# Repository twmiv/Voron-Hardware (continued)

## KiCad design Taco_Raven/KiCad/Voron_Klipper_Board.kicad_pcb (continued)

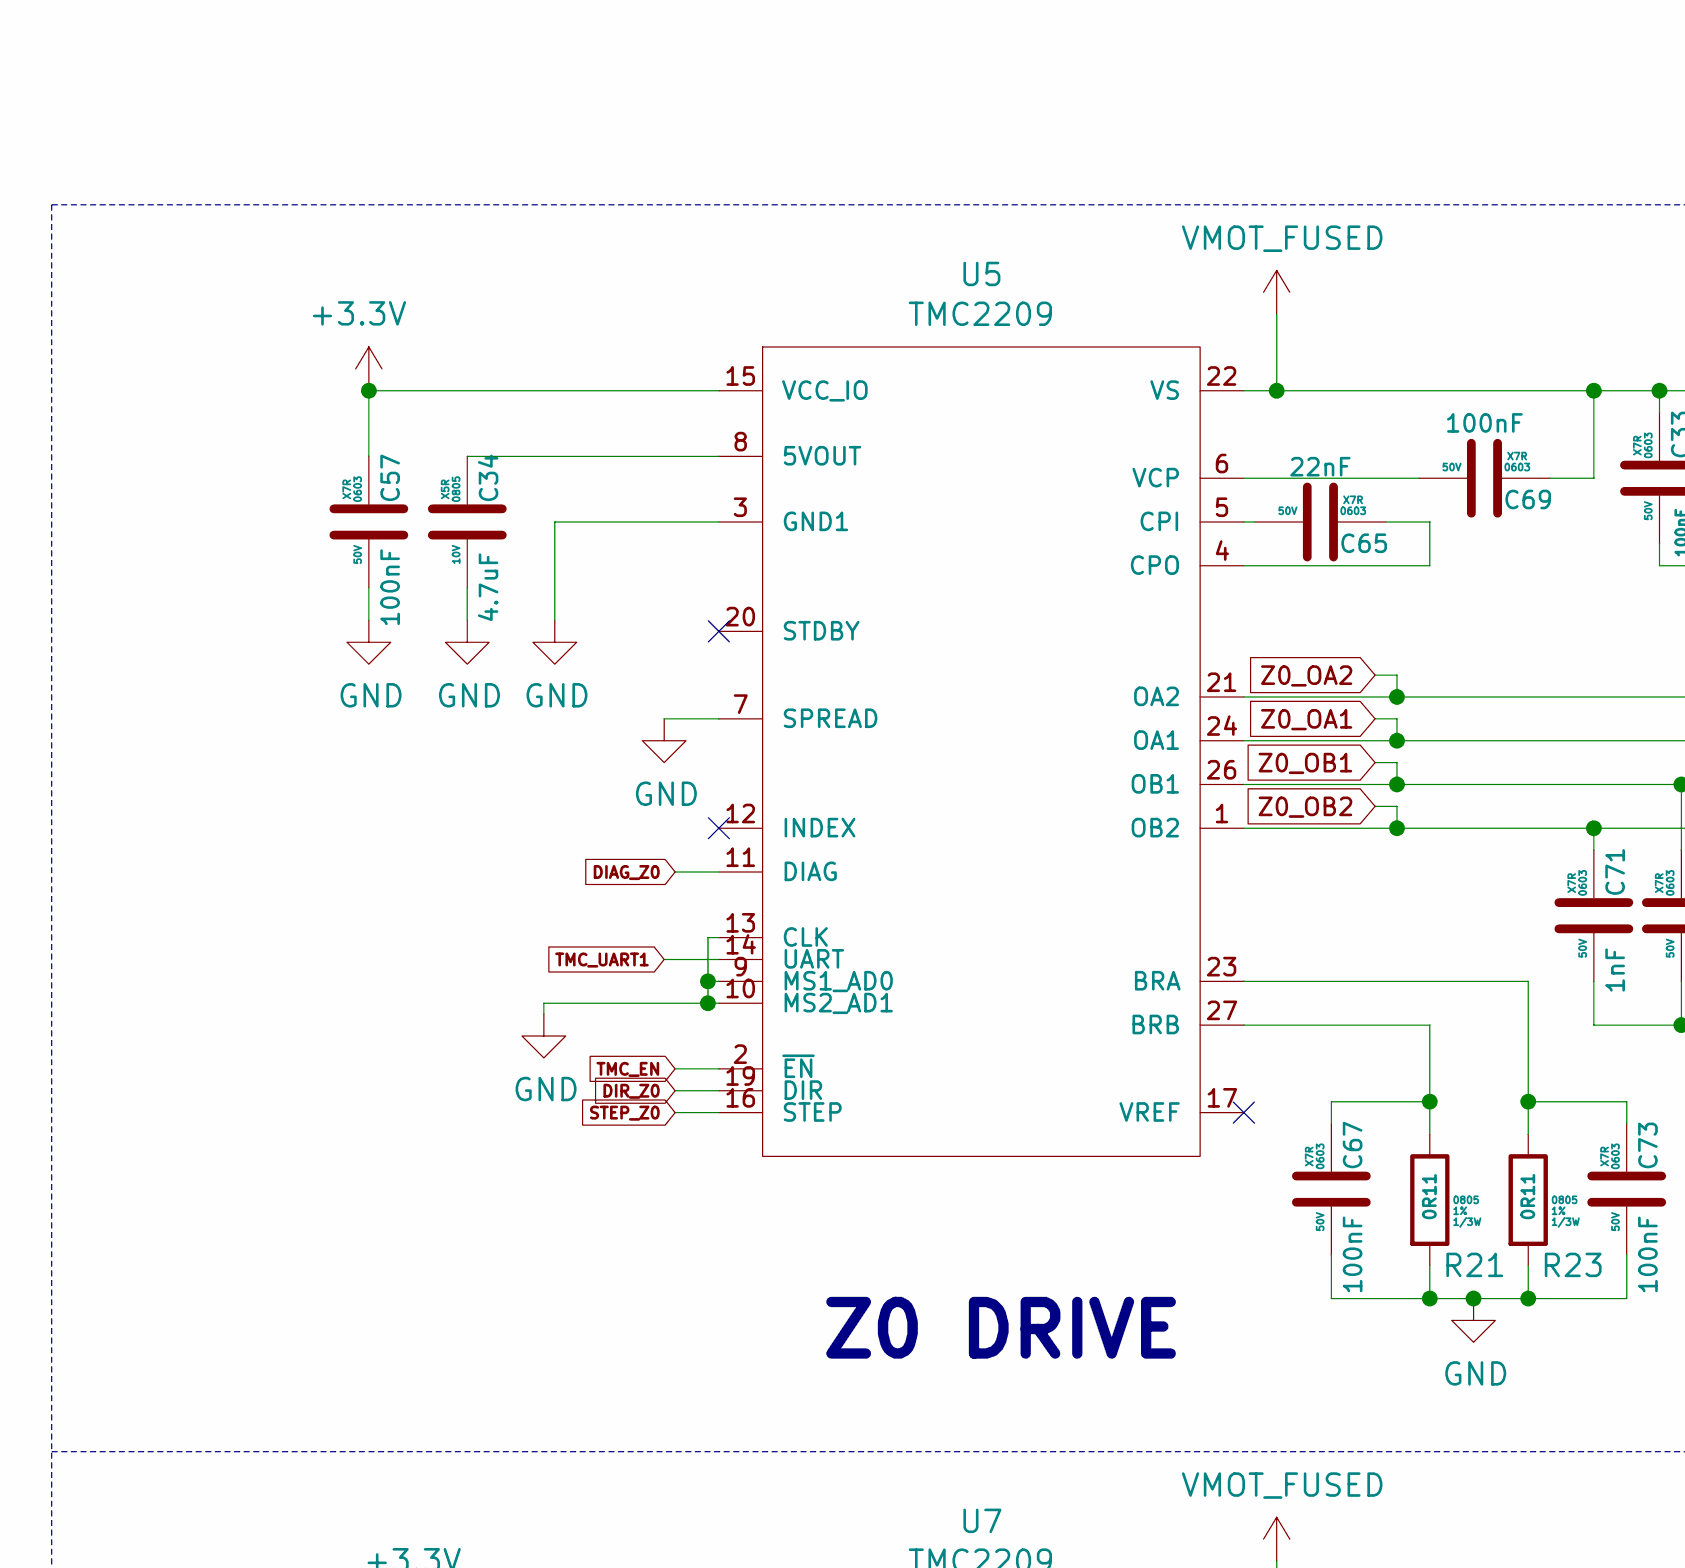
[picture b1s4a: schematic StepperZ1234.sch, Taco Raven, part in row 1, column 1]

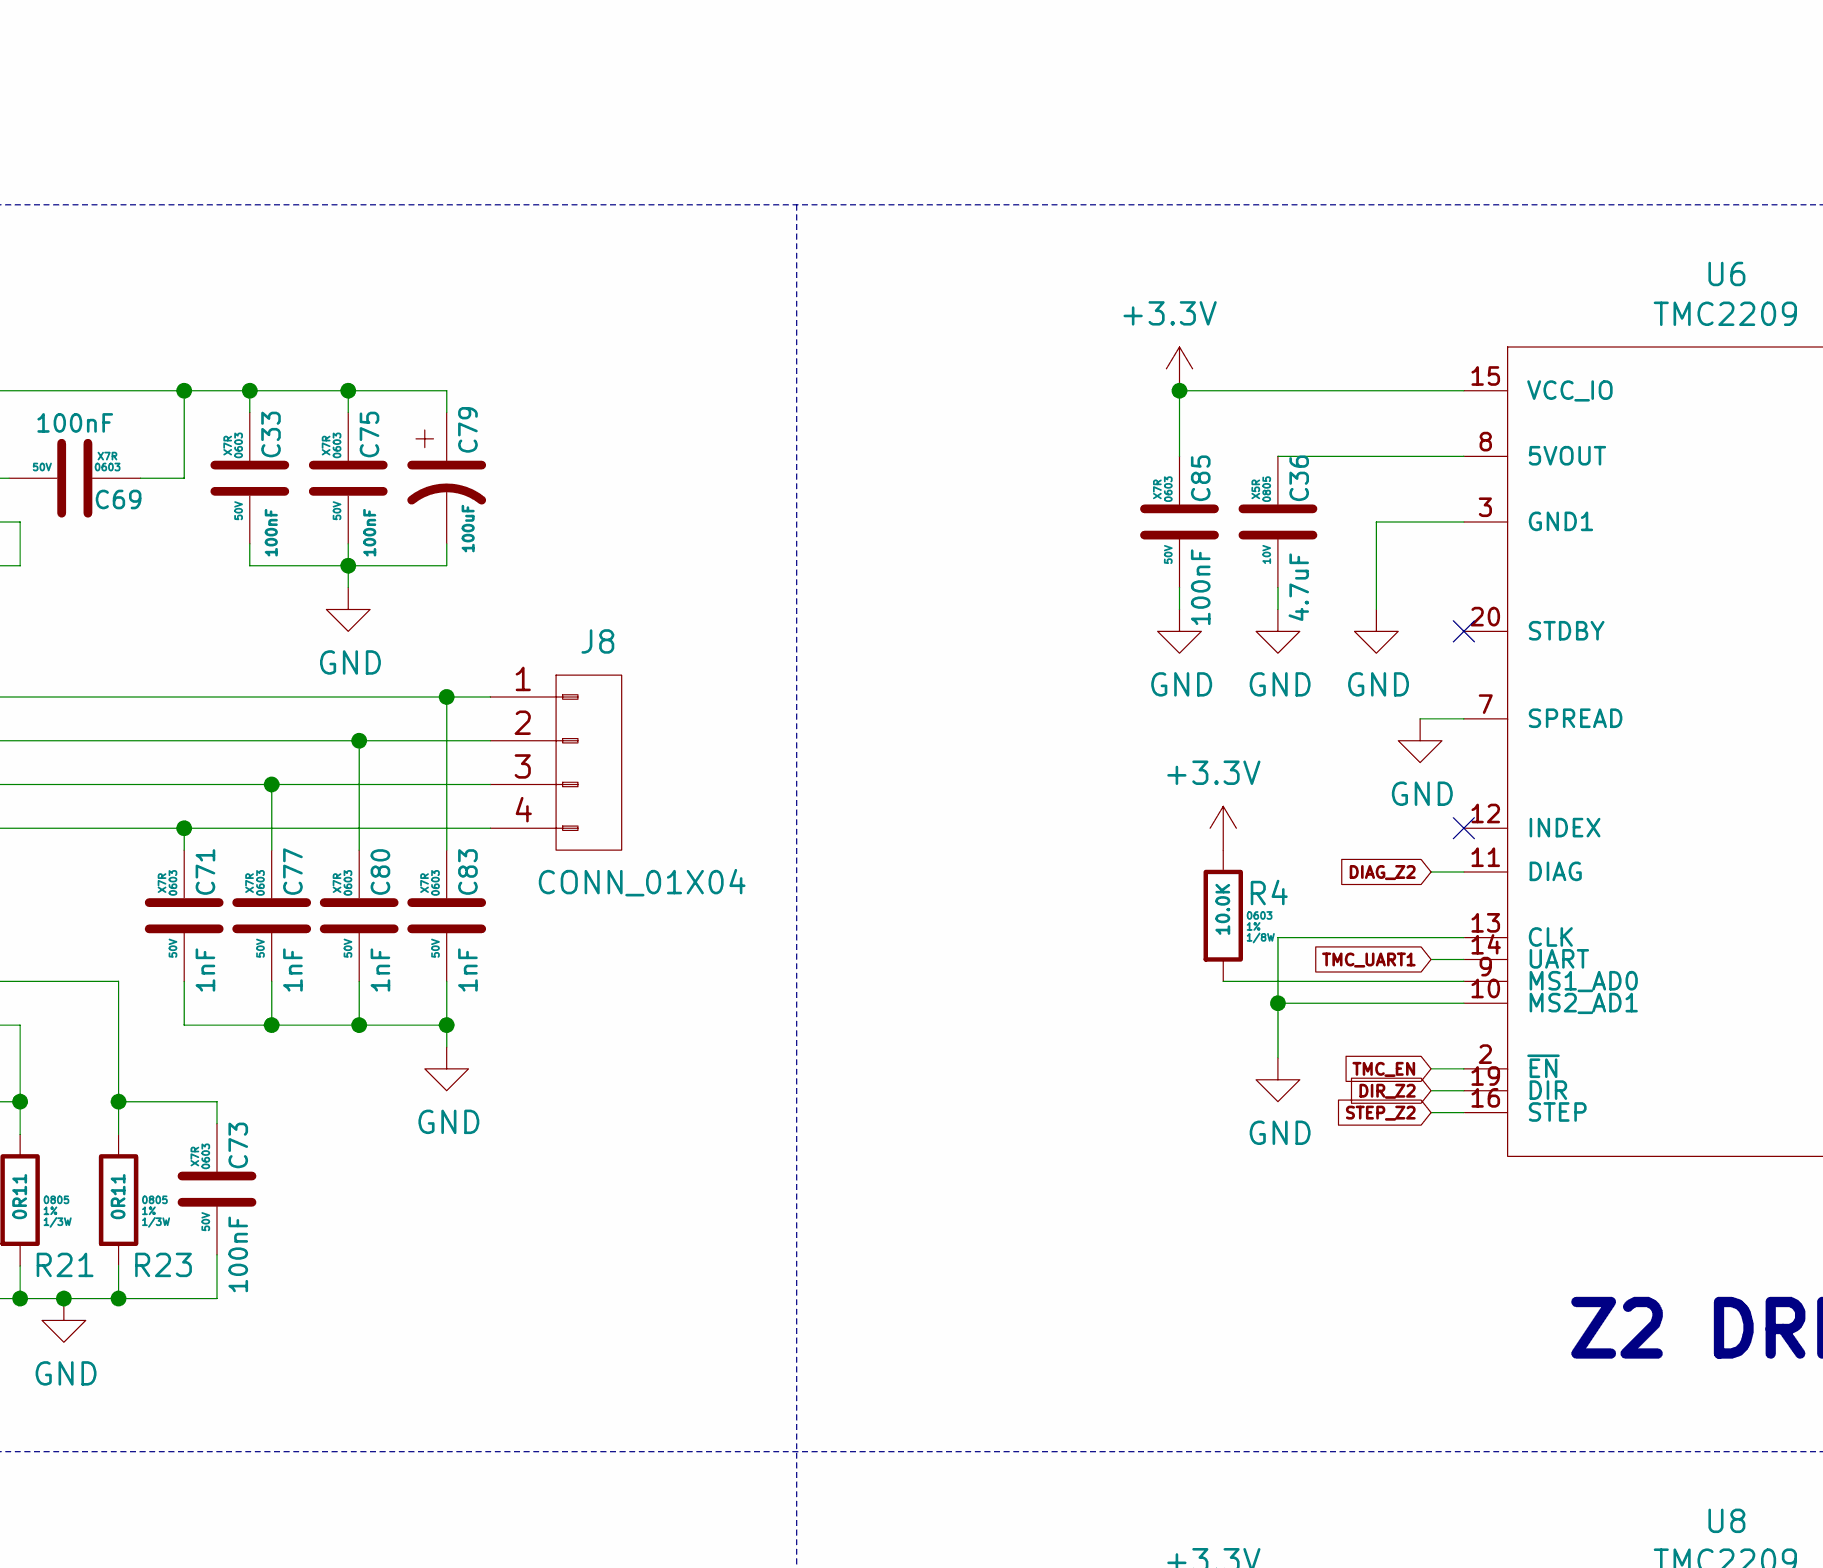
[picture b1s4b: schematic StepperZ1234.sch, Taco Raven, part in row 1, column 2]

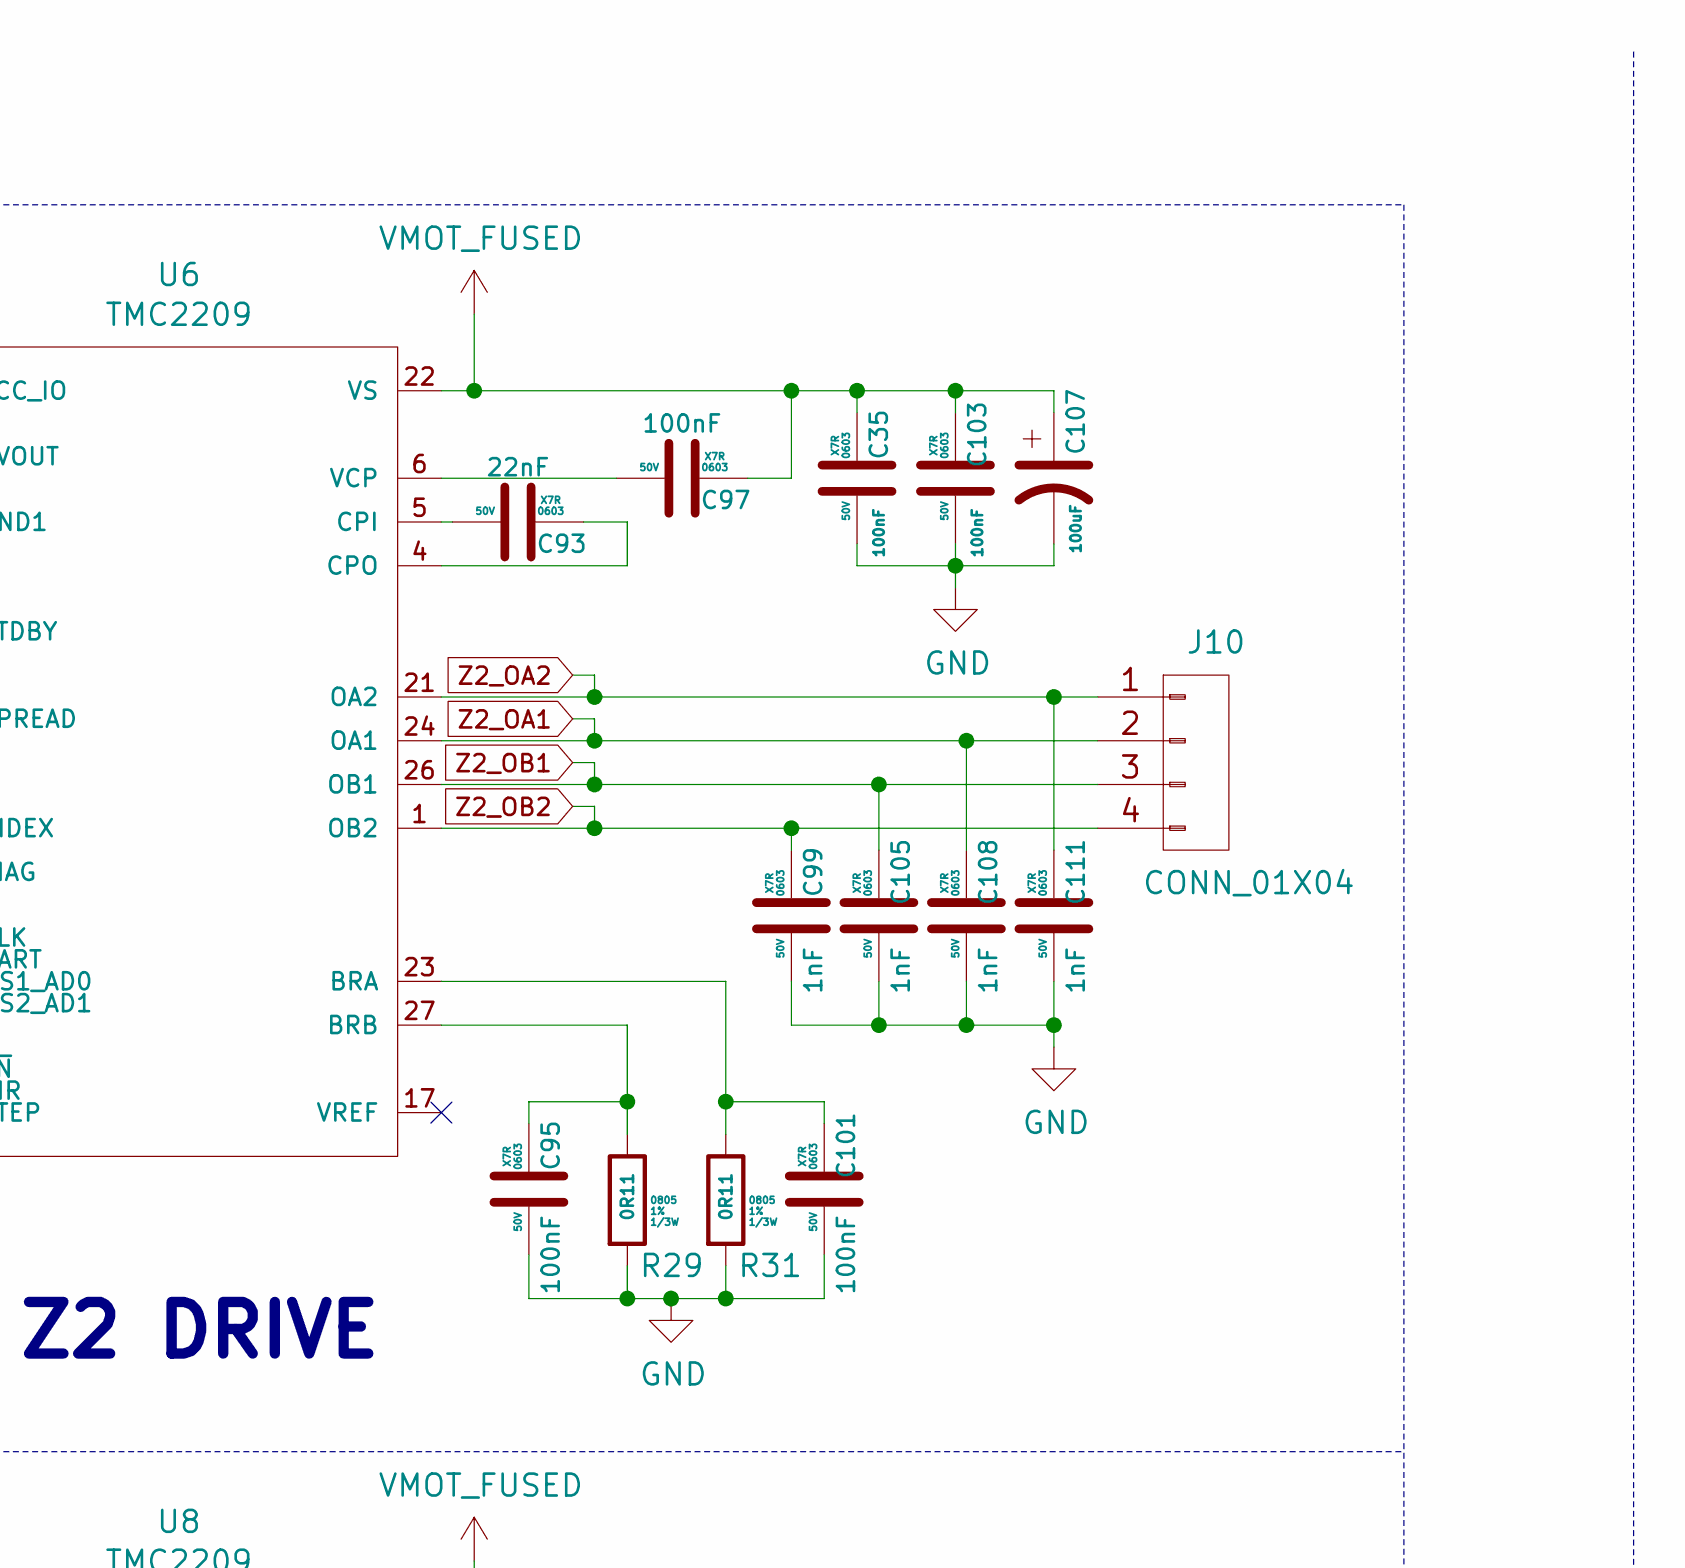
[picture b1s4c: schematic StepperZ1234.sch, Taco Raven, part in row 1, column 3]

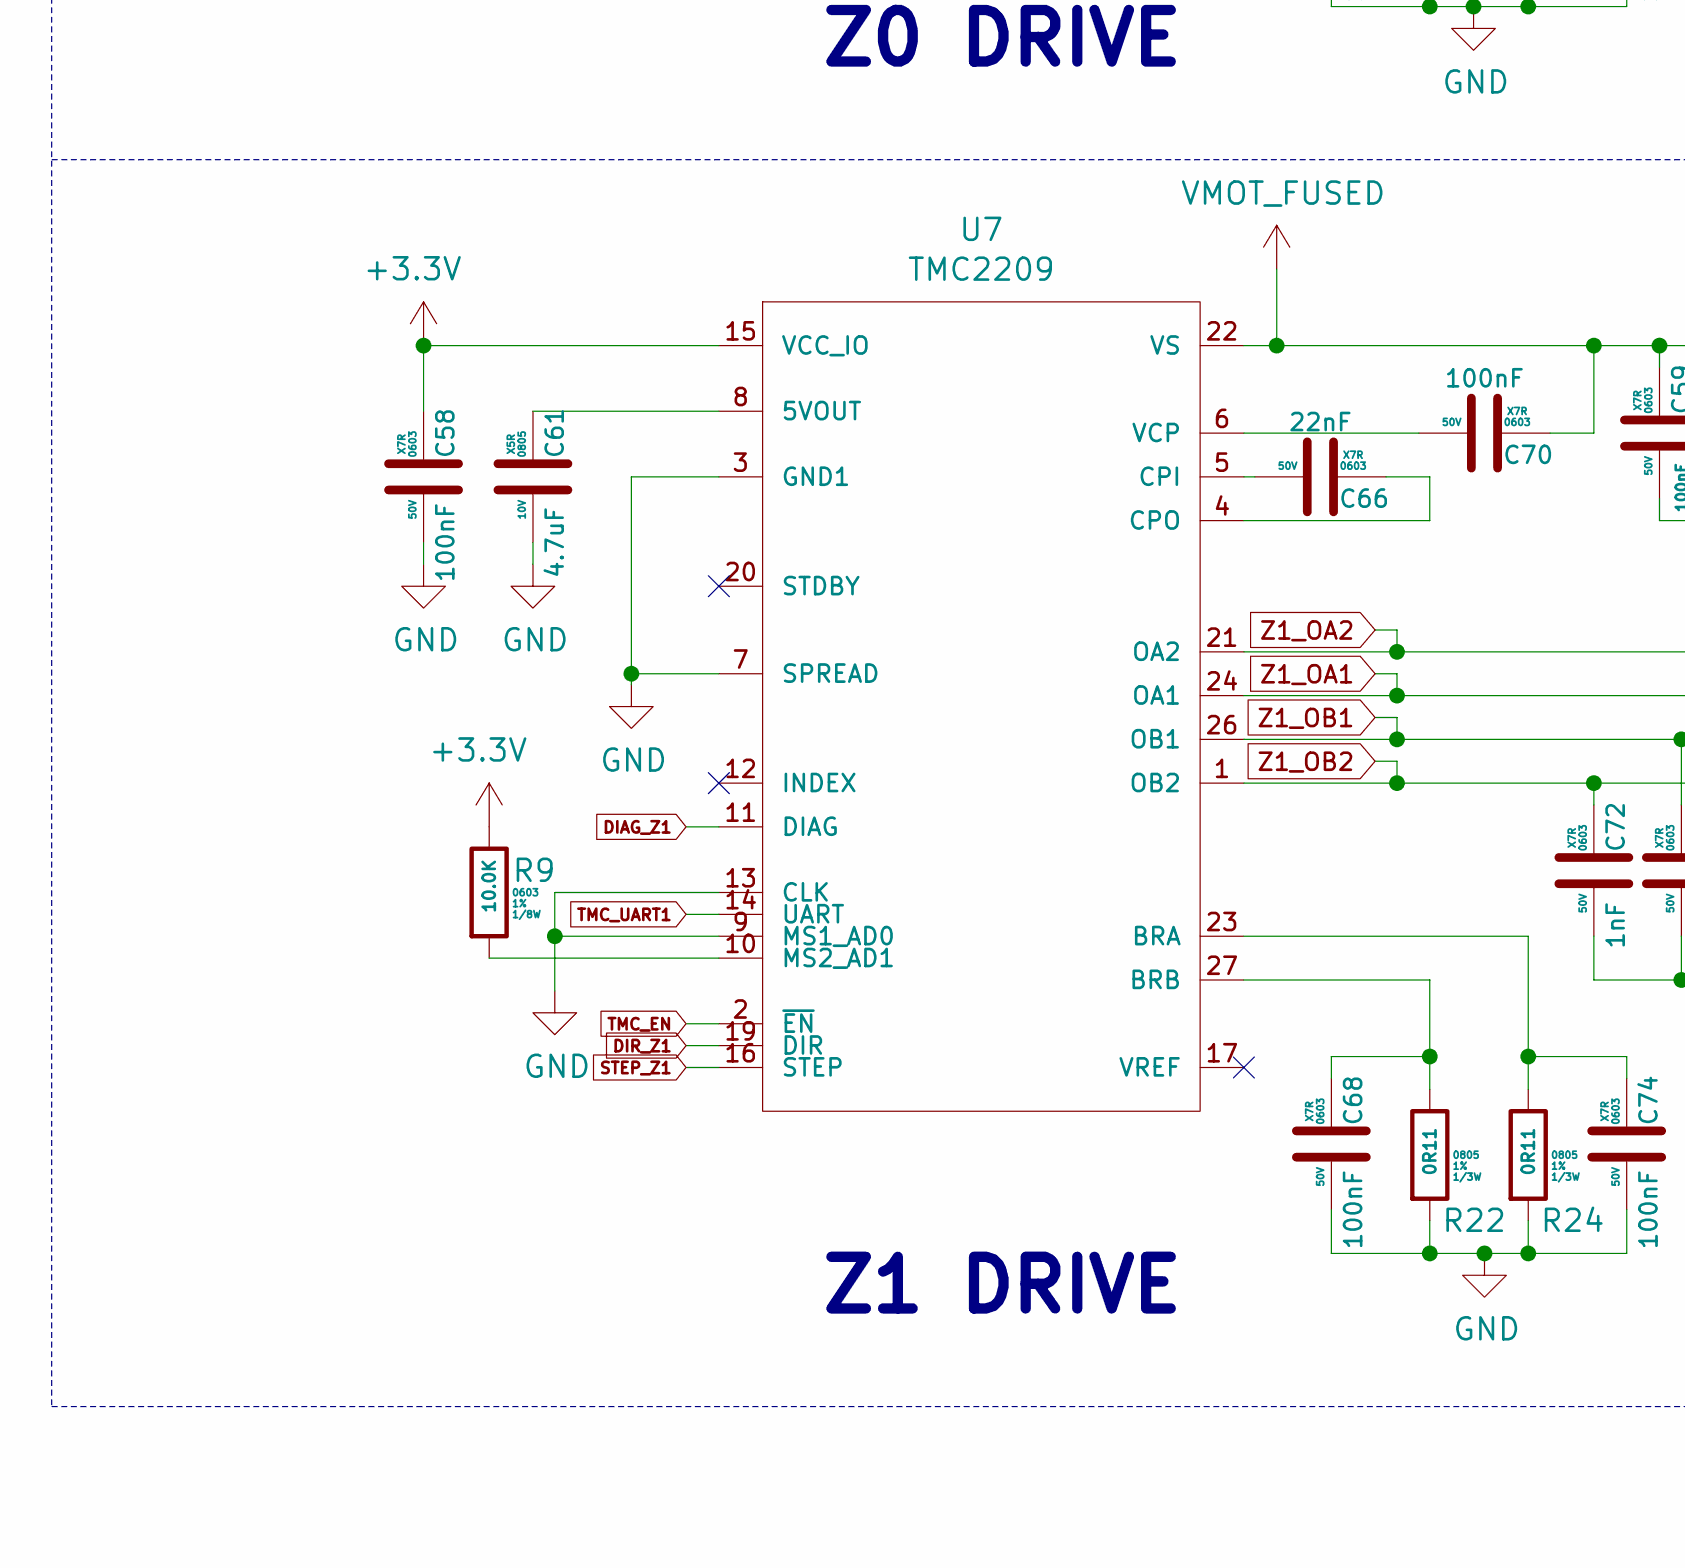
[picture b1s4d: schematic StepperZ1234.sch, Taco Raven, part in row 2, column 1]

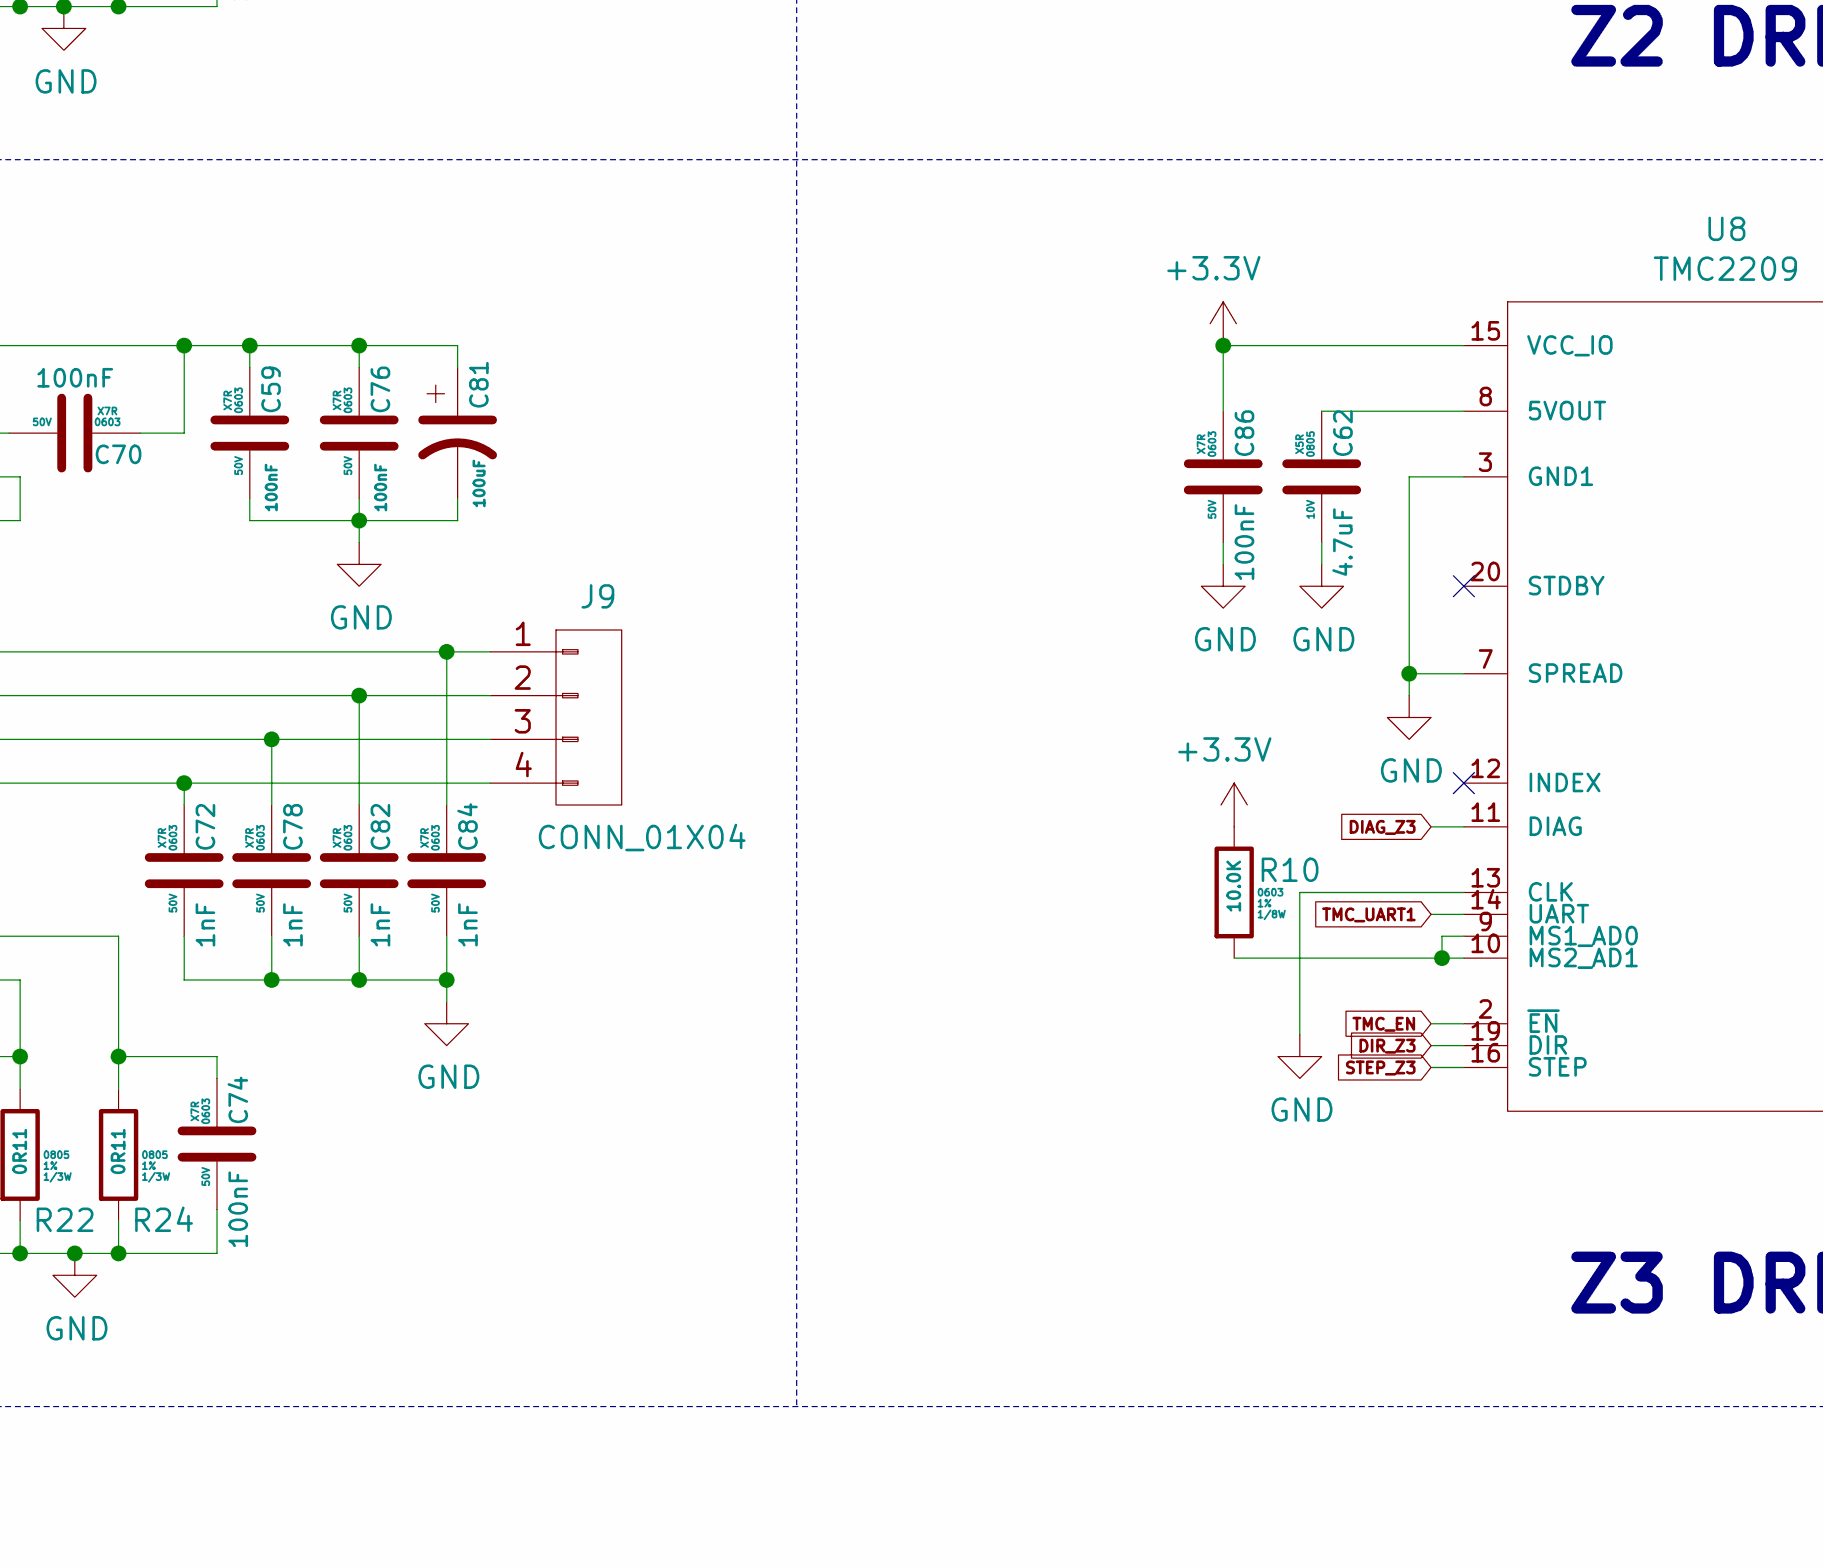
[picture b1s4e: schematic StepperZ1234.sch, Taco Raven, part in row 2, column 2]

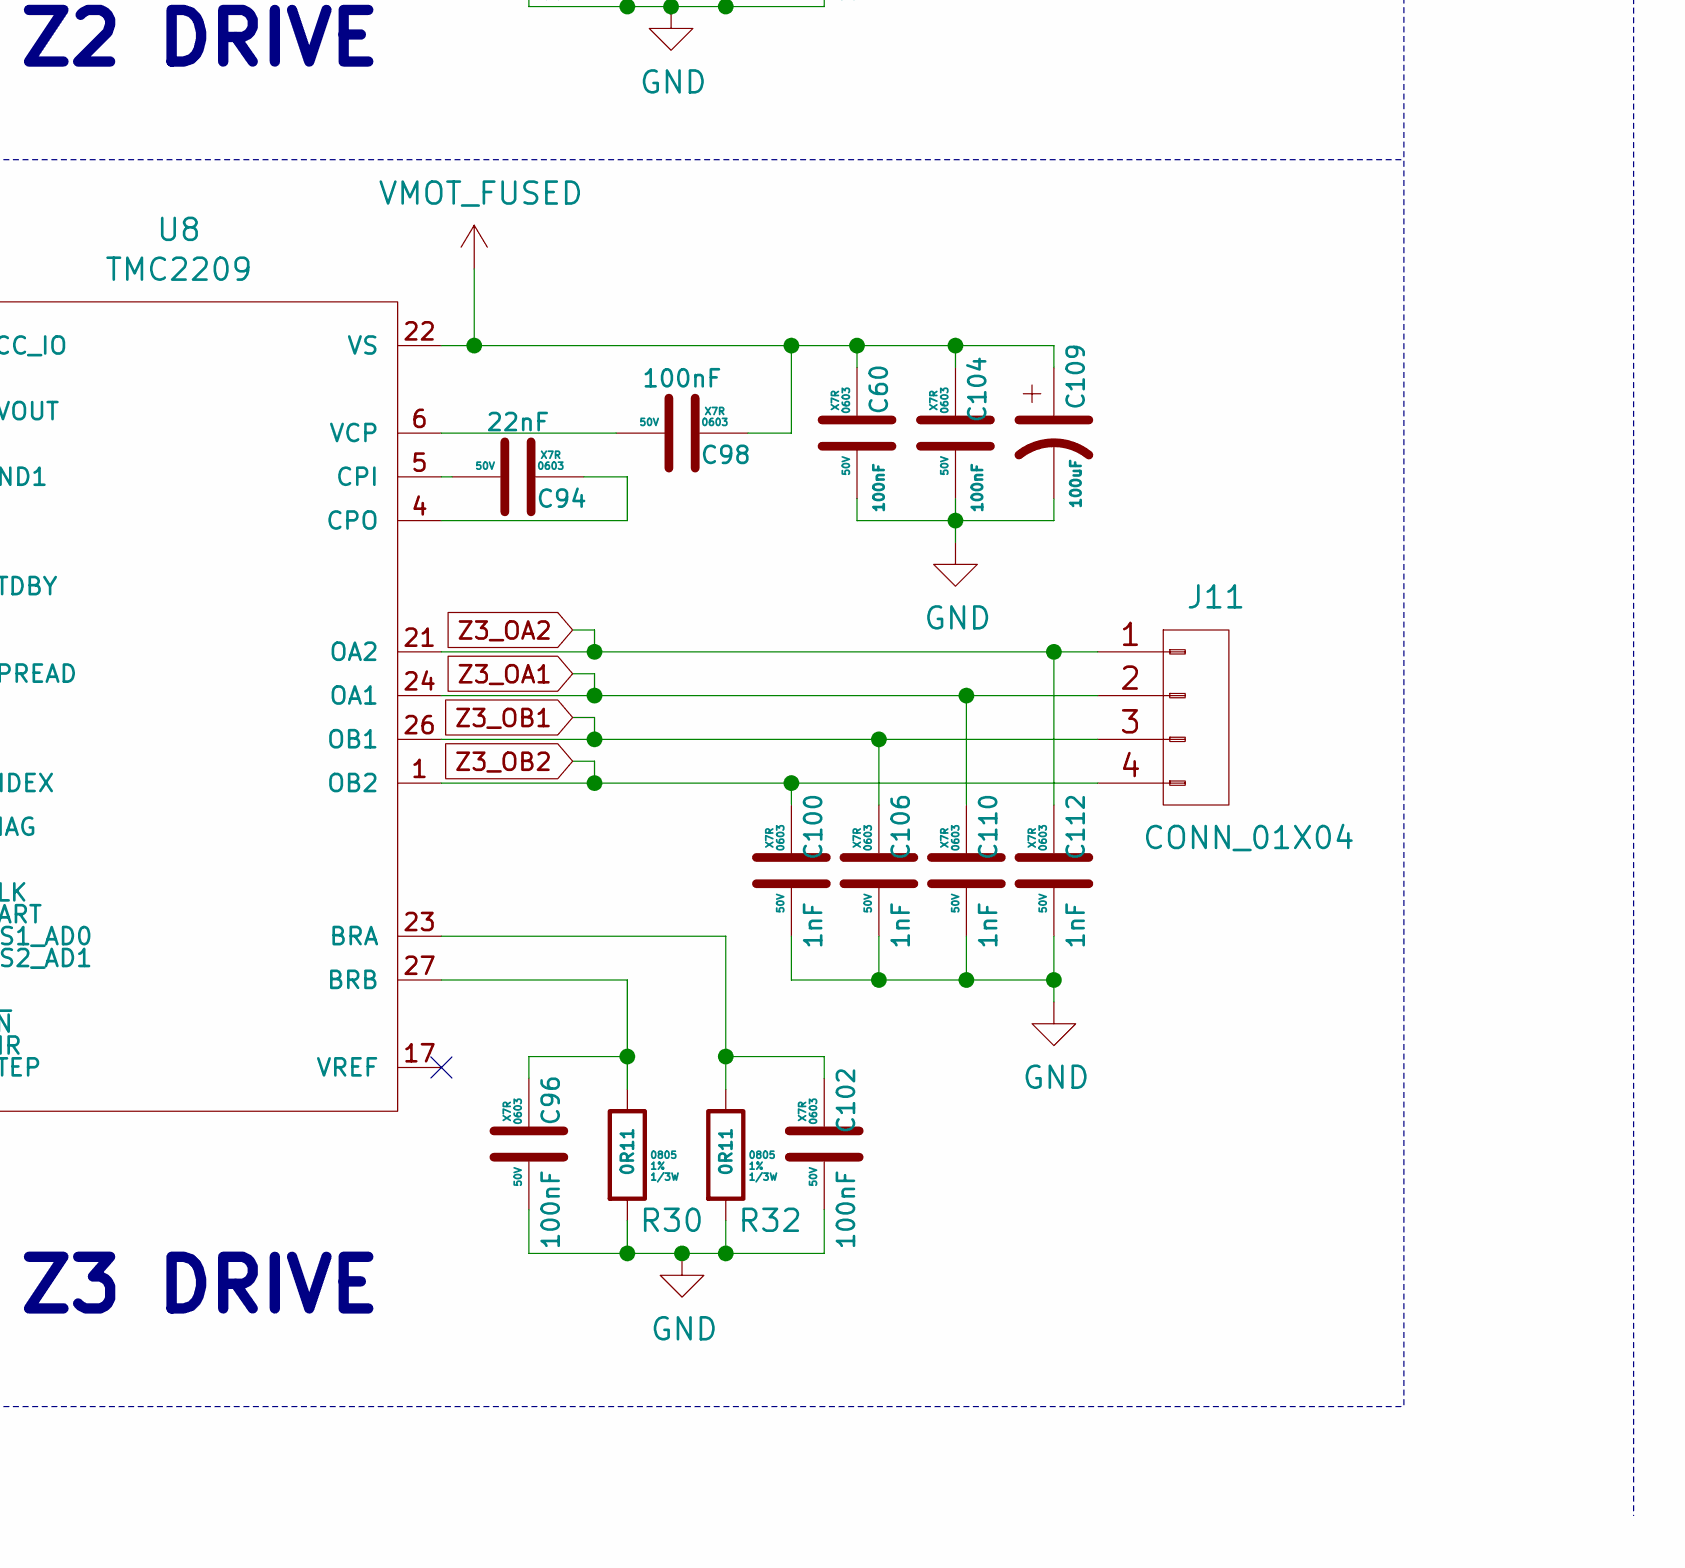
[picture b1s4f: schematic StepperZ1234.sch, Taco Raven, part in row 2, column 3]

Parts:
C33, C35, C57, C58, C59, C60, C67, C68, C69, C70, C73, C74, C75, C76, C85, C86, C95, C96, C97, C98, C101, C102, C103, C104: 100nF; C_0603; Voltage 50V; MFG PN CC0603KRX7R9BB104; Digikey P/N 311-1344-1-ND
C34, C36, C61, C62: 4.7uF; C_0805; Voltage 10V; MFG PN CL21A475KPFNNNG; Digikey P/N 1276-6464-1-ND
C65, C66, C93, C94: 22nF; C_0603; Voltage 50V; MFG PN CL10B223KB8WPNC; Digikey P/N 311-3601-1-ND
C71, C72, C77, C78, C80, C82, C83, C84, C99, C100, C105, C106, C108, C110, C111, C112: 1nF; C_0603; Voltage 50V; MFG PN CC0603KRX7R9BB102; Digikey P/N 311-1080-1-ND
C79, C81, C107, C109: 100uF; CP_Elec_6.3x7.7; Voltage 50V; MFG PN EMZR500ARA101MF80G; Digikey P/N 565-5153-1-ND
J8, J9, J10, J11: CONN_01X04; Molex_KK_1X4; MFG PN 0022232041; Digikey P/N WM4202-ND
R4, R9, R10: 10.0K; R_0603; Tolerance 1%; MFG PN RNCP0603FTD10K0; Digikey P/N RNCP0603FTD10K0CT-ND
R21, R22, R23, R24, R29: 0R11; R_0805; Tolerance 1%; MFG PN RL1220S-R11-F; Digikey P/N RL12S.11FCT-ND
R30, R31, R32: 0R11; R_0805; Tolerance 1%; MFG PN RL1220S-R11-F; Digikey P/N RL12S.22FCT-ND
U5, U6, U7, U8: TMC2209; QFN-28_EP_5x5_Pitch0.5mm

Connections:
+3.3V: C57.2, C58.2, C85.2, C86.2, R4.1, R9.1, R10.1, U5.15 (VCC_IO), U6.15 (VCC_IO), U7.15 (VCC_IO), U8.15 (VCC_IO); also elsewhere on the board
DIAG_Z0: U5.11 (DIAG); also elsewhere on the board
DIAG_Z1: U7.11 (DIAG); also elsewhere on the board
DIAG_Z2: U6.11 (DIAG); also elsewhere on the board
DIAG_Z3: U8.11 (DIAG); also elsewhere on the board
DIR_Z0: U5.19 (DIR); also elsewhere on the board
DIR_Z1: U7.19 (DIR); also elsewhere on the board
DIR_Z2: U6.19 (DIR); also elsewhere on the board
DIR_Z3: U8.19 (DIR); also elsewhere on the board
GND: C33.1, C34.1, C35.1, C36.1, C57.1, C58.1, C59.1, C60.1, C61.1, C62.1, C67.1, C68.1, C71.1, C72.1, C73.1, C74.1, C75.1, C76.1, C77.1, C78.1, C79.2, C80.1, C81.2, C82.1, C83.1, C84.1, C85.1, C86.1, C95.1, C96.1, C99.1, C100.1, C101.1, C102.1, C103.1, C104.1, C105.1, C106.1, C107.2, C108.1, C109.2, C110.1, C111.1, C112.1, R21.2, R22.2, R23.2, R24.2, R29.2, R30.2, R31.2, R32.2, U5.3 (GND1), U5.7 (SPREAD), U5.9 (MS1_AD0), U5.10 (MS2_AD1), U5.13 (CLK), U5.18 (GND2), U5.25 (GND3), U5.29 (G_PAD), U6.3 (GND1), U6.7 (SPREAD), U6.10 (MS2_AD1), U6.13 (CLK), U6.18 (GND2), U6.25 (GND3), U6.29 (G_PAD), U7.3 (GND1), U7.7 (SPREAD), U7.9 (MS1_AD0), U7.13 (CLK), U7.18 (GND2), U7.25 (GND3), U7.29 (G_PAD), U8.3 (GND1), U8.7 (SPREAD), U8.13 (CLK), U8.18 (GND2), U8.25 (GND3), U8.29 (G_PAD); also elsewhere on the board
unnamed: C34.2, U5.8 (5VOUT)
unnamed: C36.2, U6.8 (5VOUT)
unnamed: C61.2, U7.8 (5VOUT)
unnamed: C62.2, U8.8 (5VOUT)
unnamed: C65.1, U5.5 (CPI)
unnamed: C65.2, U5.4 (CPO)
unnamed: C66.1, U7.5 (CPI)
unnamed: C66.2, U7.4 (CPO)
unnamed: C67.2, R21.1, U5.27 (BRB)
unnamed: C68.2, R22.1, U7.27 (BRB)
unnamed: C69.1, U5.6 (VCP)
unnamed: C70.1, U7.6 (VCP)
unnamed: C73.2, R23.1, U5.23 (BRA)
unnamed: C74.2, R24.1, U7.23 (BRA)
unnamed: C93.1, U6.5 (CPI)
unnamed: C93.2, U6.4 (CPO)
unnamed: C94.1, U8.5 (CPI)
unnamed: C94.2, U8.4 (CPO)
unnamed: C95.2, R29.1, U6.27 (BRB)
unnamed: C96.2, R30.1, U8.27 (BRB)
unnamed: C97.1, U6.6 (VCP)
unnamed: C98.1, U8.6 (VCP)
unnamed: C101.2, R31.1, U6.23 (BRA)
unnamed: C102.2, R32.1, U8.23 (BRA)
unnamed: R4.2, U6.9 (MS1_AD0)
unnamed: R9.2, U7.10 (MS2_AD1)
unnamed: R10.2, U8.9 (MS1_AD0), U8.10 (MS2_AD1)
STEP_Z0: U5.16 (STEP); also elsewhere on the board
STEP_Z1: U7.16 (STEP); also elsewhere on the board
STEP_Z2: U6.16 (STEP); also elsewhere on the board
STEP_Z3: U8.16 (STEP); also elsewhere on the board
TMC_EN: U5.2 (~EN), U6.2 (~EN), U7.2 (~EN), U8.2 (~EN); also elsewhere on the board
TMC_UART1: U5.14 (UART), U6.14 (UART), U7.14 (UART), U8.14 (UART); also elsewhere on the board
VMOT_FUSED: C33.2, C35.2, C59.2, C60.2, C69.2, C70.2, C75.2, C76.2, C79.1, C81.1, C97.2, C98.2, C103.2, C104.2, C107.1, C109.1, U5.22 (VS), U5.28 (VS), U6.22 (VS), U6.28 (VS), U7.22 (VS), U7.28 (VS), U8.22 (VS), U8.28 (VS); also elsewhere on the board
Z0_OA1: C80.2, J8.2, U5.24 (OA1)
Z0_OA2: C83.2, J8.1, U5.21 (OA2)
Z0_OB1: C77.2, J8.3, U5.26 (OB1)
Z0_OB2: C71.2, J8.4, U5.1 (OB2)
Z1_OA1: C82.2, J9.2, U7.24 (OA1)
Z1_OA2: C84.2, J9.1, U7.21 (OA2)
Z1_OB1: C78.2, J9.3, U7.26 (OB1)
Z1_OB2: C72.2, J9.4, U7.1 (OB2)
Z2_OA1: C108.2, J10.2, U6.24 (OA1)
Z2_OA2: C111.2, J10.1, U6.21 (OA2)
Z2_OB1: C105.2, J10.3, U6.26 (OB1)
Z2_OB2: C99.2, J10.4, U6.1 (OB2)
Z3_OA1: C110.2, J11.2, U8.24 (OA1)
Z3_OA2: C112.2, J11.1, U8.21 (OA2)
Z3_OB1: C106.2, J11.3, U8.26 (OB1)
Z3_OB2: C100.2, J11.4, U8.1 (OB2)

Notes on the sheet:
Z0 DRIVE
Z1 DRIVE
Z2 DRIVE
Z3 DRIVE
